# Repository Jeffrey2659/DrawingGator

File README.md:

# DrawingGator

## Contributors and Primary Task Division

<!-- Using HTML comments. Please correct if inaccurate or not even -->
- ***Jeffrey James*** - User Interface/PC Communication (SVG/X-Y to GCode, PC UART communication to Arduino)
- ***Peek Lesh*** - Mechanical & PCB (3d Printing, part design, PCB schematic and layout design)
- ***Sara Kola*** - User Interface (Customizability, input image to SVG, SVG to ordered X-Y paths)
- ***Ethan Pena Perez*** - Simulator & Arduino (arduino-side UART and paths to motor translation)

## Project Architecture

<!-- Correct if anything outright wrong. Chat it up if we aren't sure -->
In the simplest terms, the flow of the service is the following:

**Possible Calibration Phase**
*Arduino turns on and calibrates to area* => *Arduino indicates to PC/device it is ready* => ...

**GUI Phase**
*Desktop GUI* => *Your PNG/Image* => *Image as SVG/Lines* => *Your image customization* => *Final vector image* => ...

**Translation Phase**
*Final Vector Image Points* => *GCode generator* => *GCode sent to Arduino through UART* => ...

**Parsing/Drawing Phase**
*GCode recieved and parsed on Arduino* => *translate commands to actions* => *perform next action* => ...

**Conclusion**
*Repeat parsing/drawing phase until drawing complete*.

## Setting Up the Environment

### Programming the DrawingGator Arduino
Most of the time, the Arduino should already be properly programmed, as it shall be in our demo. However, should you need to re-upload code to the arduino, the following are the recommended instructions:

1. Clone main branch of this repository
2. Install the Arduino IDE software
3. Using the Arduino IDE software, open the `DrawingGator/CustomArduinoCode/DGArduino/DGArduino.ino` file.
4. Plug in the Arduino Mega/Uno to the computer
5. Select the Arduino Mega/Uno board and port at the top left of the screen
6. Upload the code using the arrow symbol next to the board selection dropdown
7. Wait for upload to complete

This procedure is also how you apply updates. 

*Note: If you are attempting to manually communicate*
*with the Arduino using the Arduino IDE or another USB/UART control program, please refer to*
*the `README.md` file found in the `DrawingGator/CustomArduinoCode/DGArduino/` directory.*

### Running the Desktop Application

1. Clone main branch of this repository
2. Install Python and ensure it works in the terminal
3. Enter the `DrawingGator/DG_UI/` directory in the terminal
4. Run the command `python app.py`
5. Upload image from exising folder in the opened window

## Completed Work

<!-- ADD YOUR OWN COMPLETED WORK SECTION BELOW -->
**Simulator**
- To-scale display of simple mechanical parameters
  - Spool/Rotating wheel radius
  - Width & Height
- Domain restricting (Stays only in realm of possible steps with measurable degrees)
- Path making (with replacable algorithms)
  - `GREEDY` - Only chooses best next step, no consideration for looks
  - `LINE_FOLLOW` - Tries to make best next step, equally weighting line dist and goal dist
  - `CIRCULAR` - Makes the shortest path arc around a given third point from the start to the end
- Flexible point following of any count
  - Only limited by step count (customizable count in code)
- Leg-based rather than point-based simulation
  - Allows for each line of the simulator to use a different algorithm (matches G-Code more closely)
- Now allows for more than 1 step in each motor direction (up to 2 in either direction works best thus far)

**UI**
- Rudimentary UI
  - Uses Model View Presenter Architecture:
    - Model: Handles logic of UI components and different libraries integrated into the application
    - View: This section handles the layout of the GUI components and stores any triggers from the user
     - Presenter: Communicates between View and Model, to send the triggers from view to appropraite function in Model and communicates the response that needs to be reflected in view
  - Basic UI components to load image and gcode
    - Parses and cleans G code
  - Text view box to see responses from serial port and view data being sent
    - Logging responses and errors from microntroller motion library
    - Logging G Code lines
  - Configuration boxes for serial 
    - Configure Com Port
    - Configure Baud Rate
  - Functionality to send indiviudal serial commands
      - Used Pyserial to establish serial connection and process data between devices
  - Status Bar to show G code lines sent
  - Functionality for whole file G code sending

**Arduino**
- Custom Vector implementation to store GCode instruction temporarily
- UART Parsing of GCode into key-value pairs of char and double
- Validation of GCode commands with referenced table of intended arguments
- Responses to UART with debugging information if in debug mode or simple acknowledgement of `OK` when command is fully executed
- Transferred algorithm functions and structure to Arduino code
- Arduino can calculate motor steps from the 

# Libraries used for the svg_algorithm.py
1. Pillow: Image Processing
2. numpy: for numerical arrays
3. svgwrite: generate the svg file
4. matplotlib + svgpathtools: for parsing and plotting the lines

# Run the following command:
```pip install pillow numpy svgwrite matplotlib svgpathtools PyQt6 serial serialtools lxml```

**For the case of potrace since it cannot be installed through the command line:**
1. Windows:

    Download the following zip and add it to PATH: https://potrace.sourceforge.net/download/1.16/potrace-1.16.win64.zip 
    Note: Potrace is then called using the subprocess

2. MacOS: ```brew install potrace```
3. Ubuntu: ```sudo apt install potrace```

## Known Bugs & Correction Statuses

<!-- ADD YOUR OWN BUG SECTION BELOW -->
**Simulator**
- ~~Simulator linear path gets dragged to line above drawing space~~ (Fixed)
- ~~Does not identify impossible paths prior to generating, so can fail to reach goal and cap datapoints~~ (Fixed, halts operation on point no longer making progress)
- Circular path may not generate if center is between start and goal point

**UI**
- The text in the view box from the serial port is not properly formatted (FIXED)
- The status bar for the Lines sent does not update after a new g code file is loaded in over the exsisitng one
- The svg to gcode conversion does not complete fully
- If closing svg preview and command window, no way of recalling them.

**Arduino-Assembly Movement**
- Locations seem to be skewed the closer they are to the top of the board
- Occassionally the servo will be locked in an incorrect orientation and needs to be manually moved to function correctly
- Plugging in the Arduino may cause motor steps to be sent even if no commands are sent

**Serial Communication**
- The buffer is immediately filled with data and does not wait for the `OK` responses from the microcontroller

**Simulation Output**
- In some tested files there seems to be a "pen not lifted" and it drags the line when it draws. (FIXED)

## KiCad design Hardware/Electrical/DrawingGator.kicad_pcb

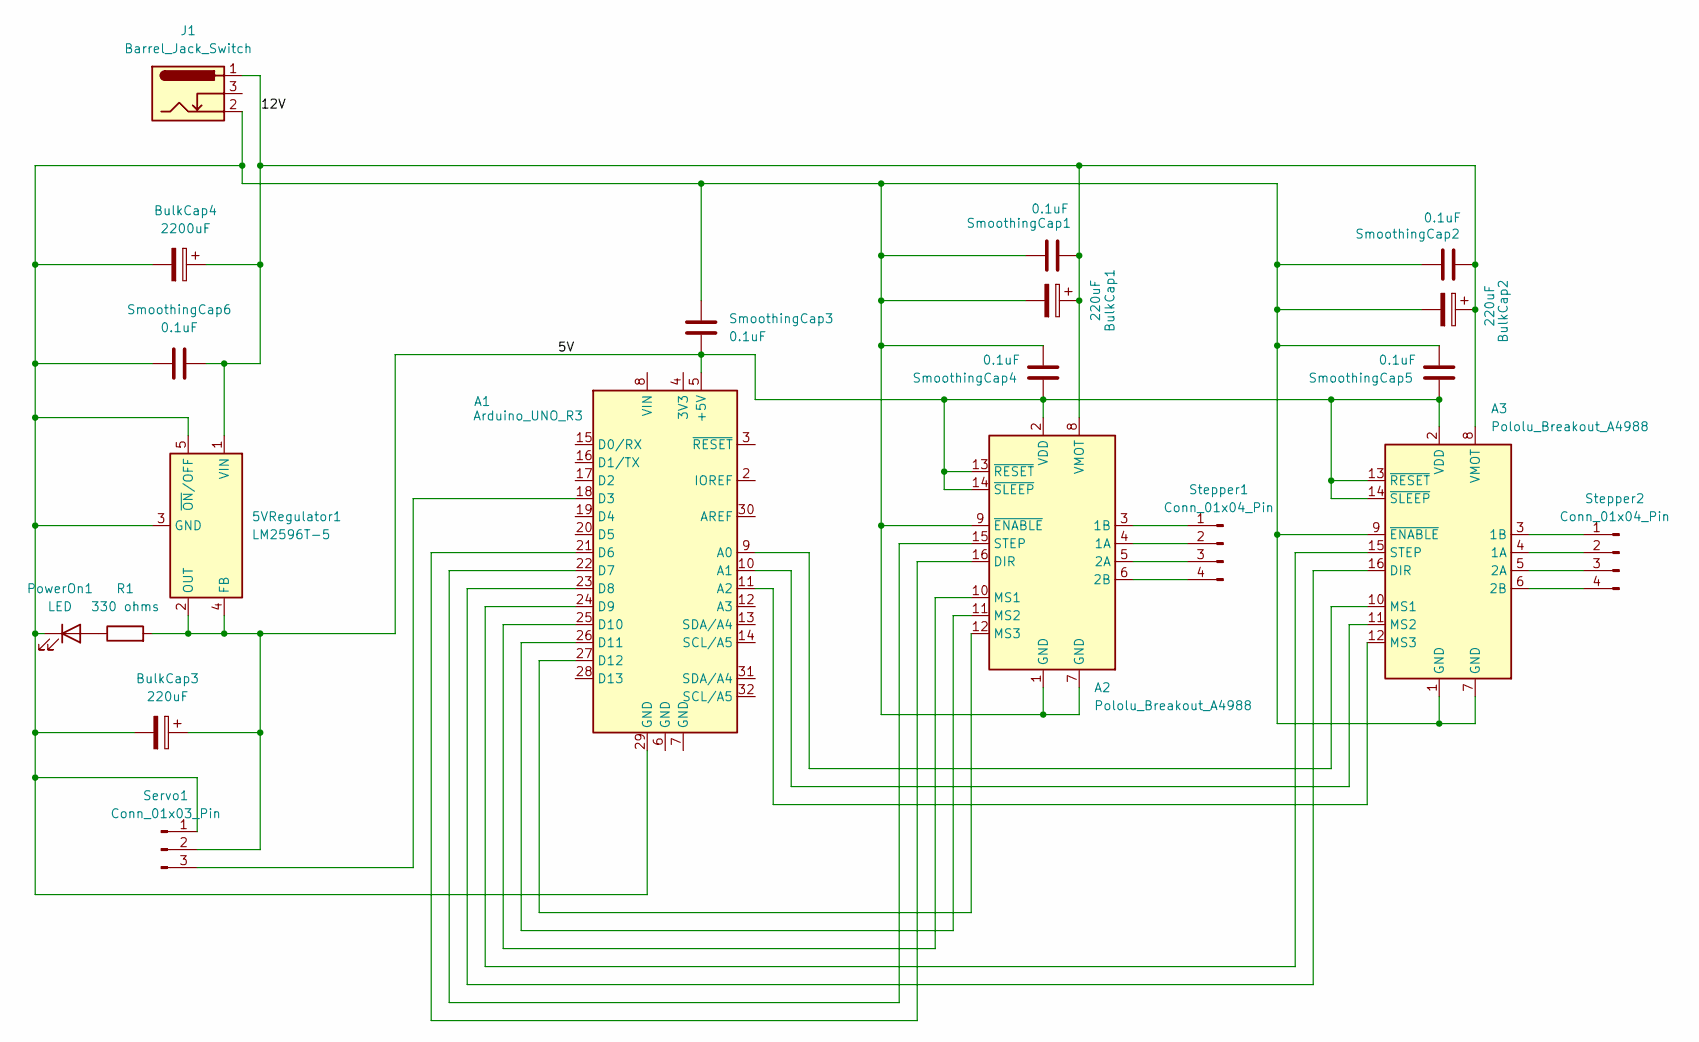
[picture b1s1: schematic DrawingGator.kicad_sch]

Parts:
5VRegulator1: LM2596T-5; TO-220-5_P3.4x3.7mm_StaggerOdd_Lead3.8mm_Vertical
A1: Arduino_UNO_R3
A2, A3: Pololu_Breakout_A4988; Pololu_Breakout-16_15.2x20.3mm
BulkCap1, BulkCap2, BulkCap3: 220uF; CP_Radial_D6.3mm_P2.50mm
BulkCap4: 2200uF; CP_Radial_D13.0mm_P5.00mm
J1: Barrel_Jack_Switch; DC_Barrel_Jack_LDC-069HS-J-005-1AG-19
PowerOn1: LED; LED_D5.0mm
R1: 330 ohms; R_Axial_DIN0207_L6.3mm_D2.5mm_P7.62mm_Horizontal
Servo1: Conn_01x03_Pin; PinHeader_1x03_P2.54mm_Vertical
SmoothingCap1, SmoothingCap2, SmoothingCap3, SmoothingCap4, SmoothingCap5, SmoothingCap6: 0.1uF; CP_Radial_D5.0mm_P2.50mm
Stepper1, Stepper2: Conn_01x04_Pin; PinHeader_1x04_P2.54mm_Vertical

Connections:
/5V: 5VRegulator1.2 (OUT), 5VRegulator1.4 (FB), A1.5 (+5V), A2.2 (VDD), A2.13 (~RESET), A2.14 (~SLEEP), A3.2 (VDD), A3.13 (~RESET), A3.14 (~SLEEP), BulkCap3.1, R1.2, Servo1.2, SmoothingCap3.2, SmoothingCap4.2, SmoothingCap5.2
/12V: 5VRegulator1.1 (VIN), A2.8 (VMOT), A3.8 (VMOT), BulkCap1.1, BulkCap2.1, BulkCap4.1, J1.1, SmoothingCap1.1, SmoothingCap2.1, SmoothingCap6.2
unnamed: 5VRegulator1.3 (GND), 5VRegulator1.5 (~ON/OFF), A1.29 (GND), A2.1 (GND), A2.7 (GND), A2.9 (~ENABLE), A3.1 (GND), A3.7 (GND), A3.9 (~ENABLE), BulkCap1.2, BulkCap2.2, BulkCap3.2, BulkCap4.2, J1.2, PowerOn1.1 (K), Servo1.1, SmoothingCap1.2, SmoothingCap2.2, SmoothingCap3.1, SmoothingCap4.1, SmoothingCap5.1, SmoothingCap6.1
unnamed: A1.9 (A0), A3.10 (MS1)
unnamed: A1.10 (A1), A3.11 (MS2)
unnamed: A1.11 (A2), A3.12 (MS3)
unnamed: A1.18 (D3), Servo1.3
unnamed: A1.21 (D6), A2.16 (DIR)
unnamed: A1.22 (D7), A2.15 (STEP)
unnamed: A1.23 (D8), A3.16 (DIR)
unnamed: A1.24 (D9), A3.15 (STEP)
unnamed: A1.25 (D10), A2.10 (MS1)
unnamed: A1.26 (D11), A2.11 (MS2)
unnamed: A1.27 (D12), A2.12 (MS3)
unnamed: A2.4 (1A), Stepper1.2
unnamed: A2.3 (1B), Stepper1.1
unnamed: A2.5 (2A), Stepper1.3
unnamed: A2.6 (2B), Stepper1.4
unnamed: A3.4 (1A), Stepper2.2
unnamed: A3.3 (1B), Stepper2.1
unnamed: A3.5 (2A), Stepper2.3
unnamed: A3.6 (2B), Stepper2.4
unnamed: PowerOn1.2 (A), R1.1

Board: 2 copper layers, 20 parts (0 on the bottom side), 23 nets, no tracks yet.

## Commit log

2025-09-24 Testing Commits
2025-09-24 Testing Commits 1
2025-09-24 Making Sure Commits R Right
2025-10-11 Stepper Motor Sanity Check
2025-10-12 Interface
2025-10-16 Pyqt Learning Code
2025-10-16 Intial UI for DG
2025-10-17 simple svg
2025-10-17 did an uppsies
2025-10-17 removed a file
2025-10-20 Updated Code: Serial Streaming is still broken albeit
2025-10-22 potrace
2025-10-23 Fixed serial streaming and added single command send
2025-10-23 recent changes
2025-10-23 Marlin Motion planning
2025-10-26 Initial Commit
    Added existing files to version control. Working on pre-alpha document and planning merges
2025-10-26 Updated README
    Reformatted README and added information necessary for pre-alpha
2025-10-26 recent tweaks to UI
2025-10-26 updated readme for UI
2025-10-26 made some changes here and there
2025-10-26 added a known bug to readme
2025-10-27 added the bug in readme of main
2025-10-27 got rid of a few lines
2025-10-27 Updated Pulley Simulator.rbxl
    Created separate parallel running simulation environment, started work for circle algorithm (CW and CCW)
2025-10-27 Update README with libraries
    Added libraries used for svg_algorithm.py and installation instructions for Potrace.
2025-10-29 trying to add algorithm to interface
2025-10-29 Simulates Separate Algos in 1 Model
    Can now simulate multiple legs with different algorithms within the same model. Fixed bug of infinite attempts to generate points when stuck
2025-10-30 Added display function and the simualtion is not working when called in UI
2025-10-30 Added circular paths, updated readme
2025-10-30 Revert "Added display function and the simualtion is not working when called in UI"
    This reverts commit 1df58dd9b59965aa18ac7abb465e31ae23717102.
2025-10-30 Added new function for displaying SVG, animation does not work with UI
2025-10-30 Added stuff
2025-10-30 Added README to CustomArduinoCode
2025-10-30 display window now added to app.py
2025-10-30 Updated Arduino code to have simulator algorithm code
2025-10-30 Updated Arduino File for Vector Implementation
    Created vector implementation within arduino code file for use with parsing G-Code. Didn't realize it didn't exist until halfway through working through possible solutions, so just went ahead and mad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
2025-10-31 Arduino Code Modular Refactor and GCode Parsing
    Can now parse G-Code commands and respond with component
2025-11-02 Fixed config file for the standard of G code we want
2025-11-02 got potrace working for my install path still need to make it robust
2025-11-03 add Sara code, still a few bugs
2025-11-03 Created structures for executing commands
2025-11-04 added svg to gcode pipeline, bugs still persist
2025-11-04 Added extra m commands, refactored GCodeHandler.h
2025-11-04 Patched stuff together, but stil need to make paths universal and get it running
2025-11-04 Fixed i hope, potrace doesn't work for me, but that a me thing
2025-11-06 Added StateHolder class to share actions amongst instances
2025-11-06 added a few comments
2025-11-09 Added error module, implemented execution actions for states
    Added error module to print out specific errors
    Updated leg and point data to be printable, legs now have valid bool
    GCodeHandler now holds pointer to StateHolder to manage command queue
    GCodeHandler now executes instructions on StateHolder
    StateHolder now holds leg queue data
2025-11-09 Update installation command in README
    Added PyQt6, serial, serialtools, and lxml to installation command.
2025-11-10 Working on UI and adding new window
2025-11-10 Making changes to UI, making it pretty pretty
2025-11-11 Upload File takes directly to images
2025-11-13 update gitignore
2025-11-13 Split AlgorithmItems, added motor direct override functionality
    Split AlgorithmItems.h into AlgorithmClasses (holding Algorithms enum, Point class, and LegData class) and AlgorithmMethods
    Added GCode direct functionality to servo motor (Passing)
    Added GCode direct functionality to move stepper motor (WIP, maybe motor driver connection issue?)
2025-11-13 fixed potrace issue(im 90% sure) and got animation generating for svg and other img type
2025-11-13 fixed progress bar, not resetting
2025-11-13 Updated motor control commands and state behavior
2025-11-14 Updated for first attempt at run
2025-11-15 Corrected pathing and added reference offset, yet to be tested
2025-11-15 Generated a Readme
2025-11-15 Added more to readme
2025-11-15 updated config.toml
2025-11-16 small changes to readme
    Fixed formatting issues in the UI and simulation output.
2025-11-16 Final fixes from Yesterday evening (forgot to push)
2025-11-17 updated parsing and g code generation
2025-11-17 removed grbl
2025-11-17 update config
2025-11-18 exper
2025-12-09 saving everything incase of computer issue
2026-01-15 just updating my branch with main
2026-01-15 pushing old minor number change for down vs up pen
2026-01-16 Fixed the extra pendowns instructions and did a lil code cleanup
2026-01-16 research documentation
2026-01-20 research on edge detection
2026-01-22 PCB research
2026-01-23 switching to open cv for better edge detection
2026-01-23 something is not working on my end
2026-01-23 removed some lines
2026-01-26 new changes for number of strokes
2026-01-26 cleaning up branch
2026-01-26 more cleaning
2026-01-26 Revert "Merge pull request #14 from Jeffrey2659/Interface"
    This reverts commit 89e1c0305ee1543e6cb784c0ceb391510005d80f, reversing
    changes made to 1bcaeacccd0669e1afe9ac8cdc03780cd64dea6b.
2026-01-26 new code
2026-01-26 cleaning
2026-01-26 Made new copy of code and began refactoring
    Made old code (ArduinoCodeGreedy) and new code (ArduinoCodePathing) directories.
    Refactored names of Vector to ArrayList and Point to Vector2d
2026-01-26 added svg preview for uploading gcode
2026-01-26 Moved movements to separate file
2026-01-26 changes to fix line issue
2026-01-27 Added speed parameter and began work on implementing direct pathing system
2026-01-27 Able to send move instruction at high speed
2026-01-30 time logs for jan... forgot to upload...
    i'll be better about this.
2026-02-02 removed __pycache from commits
2026-02-02 added a way to bring back svg preview window
2026-02-02 Mild refactoring to remove unused functions and update current position after each step is made.
    curpos is now real position, not canvas position
2026-02-02 Fixed Inability to send multiple move commands, working on speed inconsistency
    3:30-6PM
2026-02-03 made changes to threshold, there were issues and lines were not being processes/were being removed
    worked from 8pm-10:15pm to get the issue working, ended up manually removing the border that appeared after threshold
2026-02-03 adding testing capablity
2026-02-03 Attempting to debug rapid inconsistent movement
2026-02-05 making changes to how images are processed
2026-02-09 making changes to detect colors, there are errors right now
2026-02-10 have color detection somewhat working now
2026-02-10 more testing modules added
2026-02-10 remove uncessar modules marlina nd grbl
2026-02-10 remove pycache files
2026-02-10 gitignore files update
2026-02-10 gitignore
2026-02-10 FIxed speed inconsistency, need to address position drift
    Successfully interfaces with UI now
2026-02-12 working on getting better colors/more colros
2026-02-16 working on getting better colors and less lines of svg if possible
2026-02-16 made changes to preview of app
2026-02-17 Rename electrical time logs.txt to all_logs_design2.txt
2026-02-17 Rename 1-30.txt to jan_30.txt
2026-02-17 Rename laptop_blackout_issue_1-16.docx to jan_16.docx
2026-02-17 Rename research_PCB_1-19_1-21.docx to jan_1-19_1-21.docx
2026-02-17 Create feb_16
2026-02-17 Renamed Folders
2026-02-17 Added Electrical Folder
2026-02-17 homing for system
2026-02-18 working on writing with text
2026-02-18 Create feb_18
2026-02-18 new branch to work on color stuff
2026-02-18 reverted back to grayscale for main
2026-02-19 new front page
2026-02-22 Create feb_21
2026-03-03 added toggle switch to view both grayscale/color
2026-03-03 speed control and easier connection
2026-03-03 combined front page and main ui screen
2026-03-09 new layout
2026-03-10 new layout + new colors + new UI
2026-03-10 Corrected false resets for pins between moves, supports for relative and mm modes
2026-03-24 new layout almost done
2026-03-25 stop
2026-03-26 new changes
2026-03-29 added new button to override the connection to arduino
2026-03-31 Bugfixing in restarting logic, added microstep skeleton
2026-04-08 addeded stop button
2026-04-09 better algorithm done
2026-04-09 small changes to UI
